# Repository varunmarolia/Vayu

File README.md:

# Vayu
Vayu is a smart ventilation system with heat recovery

# Problem
During winter time when the temperature is in single digit or below, the windows are kept shut and sealed so that radiators can work their magic.
The quality of indoor air gets very bad as the day goes by. The current ventilation system is basically a hole (ranging rom 100mm to 150mm in diameter) in the wall with some filter and vent with open/close mechanism.
This system does not provide enough air flow inside room specifically when the room is sealed. In order to make the indoor quality better the air needs to be forced/pumped inside the room.
Since the outside temperature is very low it needs to be heated and filtered before it can be pulled inside the room. 

# Focus of the project
- The aim of the project is to provide a ventilation system that can provide fresh room temperature air. We do this by recovering the heat from the air in the room itself.
- The system must be smart enough such that the "Heat recovery" should be performed automatically. i.e. if the outside temperature air is cold, turn on the heat recovery, if not just do normal ventilation.
- The design must be a quiet one, so we can sleep peacefully.
- Proper condensation management and defrosting functions.
- The system should have wireless capabilities in order to be an IoT device in the future.

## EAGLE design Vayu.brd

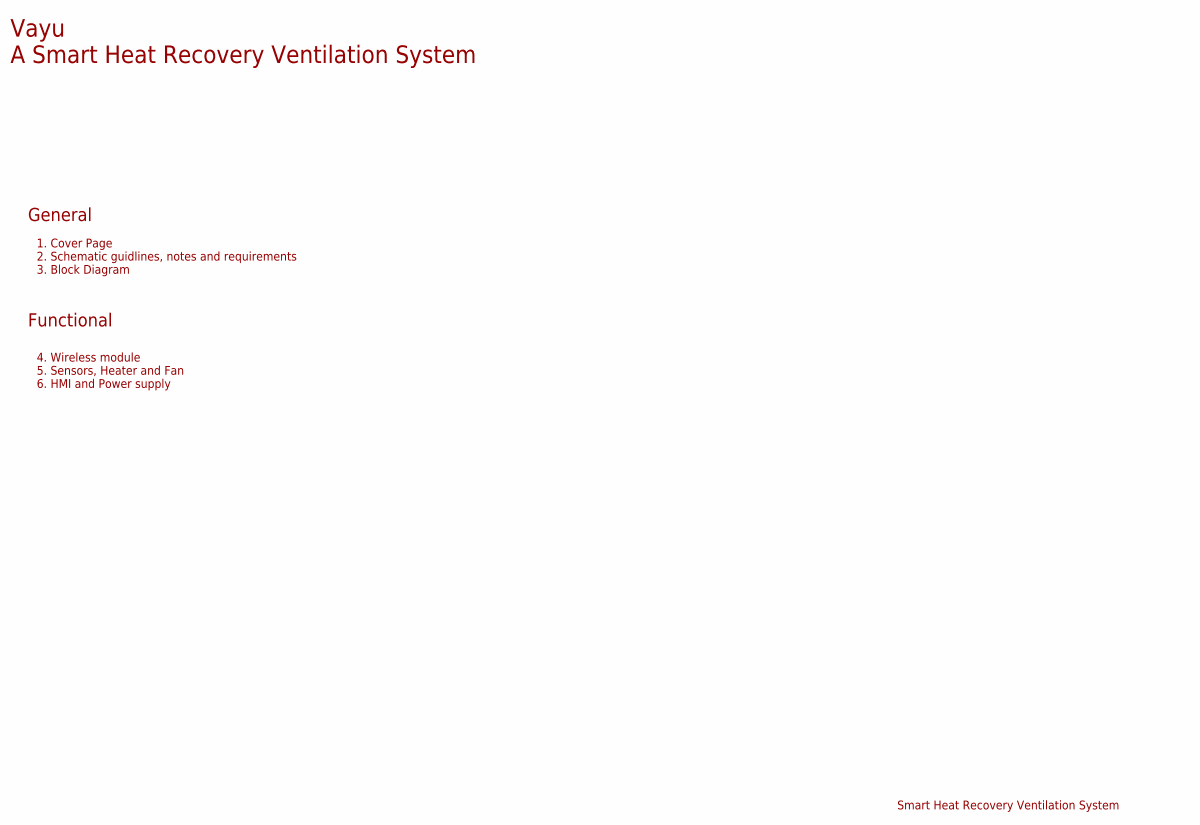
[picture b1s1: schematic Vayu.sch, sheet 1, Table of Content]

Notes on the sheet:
Smart Heat Recovery Ventilation System
General
1. Cover Page 2. Schematic guidlines, notes and requirements 3. Block Diagram
Functional
4. Wireless module 5. Sensors, Heater and Fan 6. HMI and Power supply
Vayu A Smart Heat Recovery Ventilation System

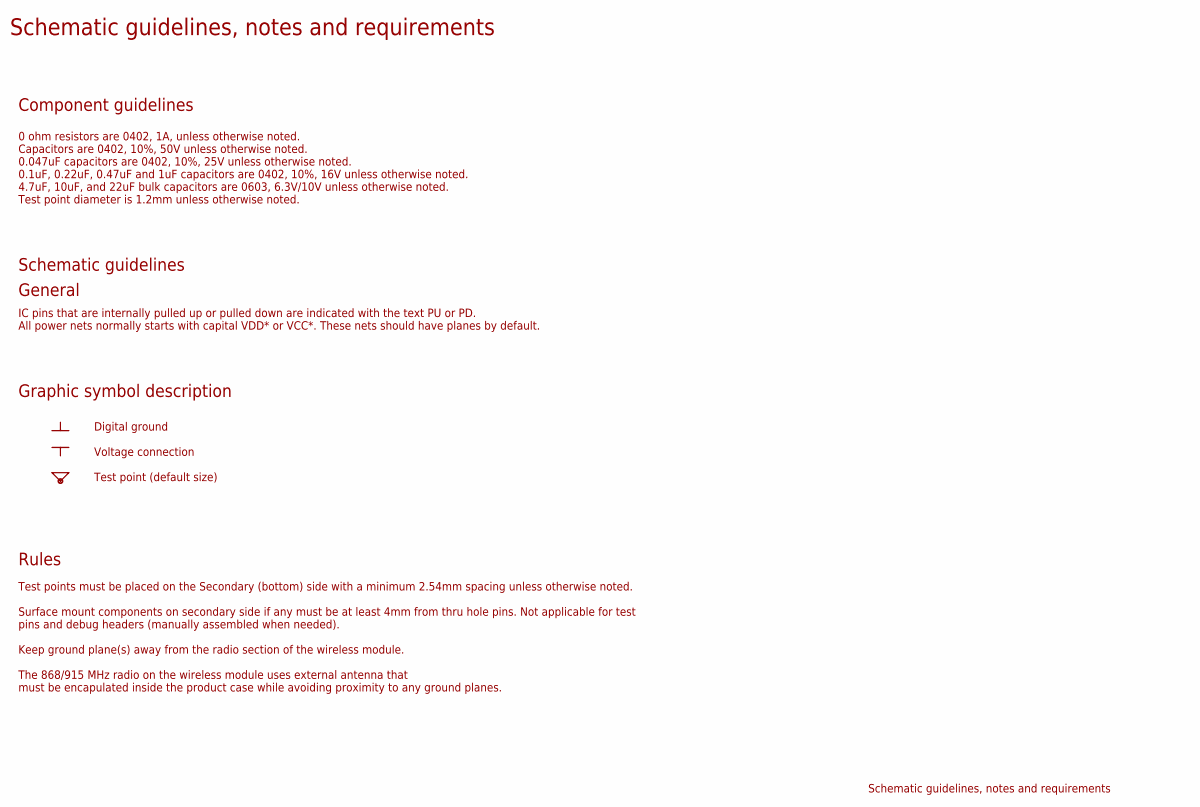
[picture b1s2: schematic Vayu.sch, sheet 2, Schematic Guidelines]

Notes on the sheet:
Schematic guidelines, notes and requirements
Component guidelines
0 ohm resistors are 0402, 1A, unless otherwise noted. Capacitors are 0402, 10%, 50V unless otherwise noted. 0.047uF capacitors are 0402, 10%, 25V unless otherwise noted. 0.1uF, 0.22uF, 0.47uF and 1uF capacitors are 0402, 10%, 16V unless otherwise noted. 4.7uF, 10uF, and 22uF bulk capacitors are 060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
Schematic guidelines
General
IC pins that are internally pulled up or pulled down are indicated with the text PU or PD. All power nets normally starts with capital VDD* or VCC*. These nets should have planes by default.
Graphic symbol description
Digital ground Voltage connection Test point (default size)
Rules
Test points must be placed on the Secondary (bottom) side with a minimum 2.54mm spacing unless otherwise noted. Surface mount components on secondary side if any must be at least 4mm from thru hole pins. Not applicable for test pins and debug headers (manually assembled when needed). Keep ground pl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

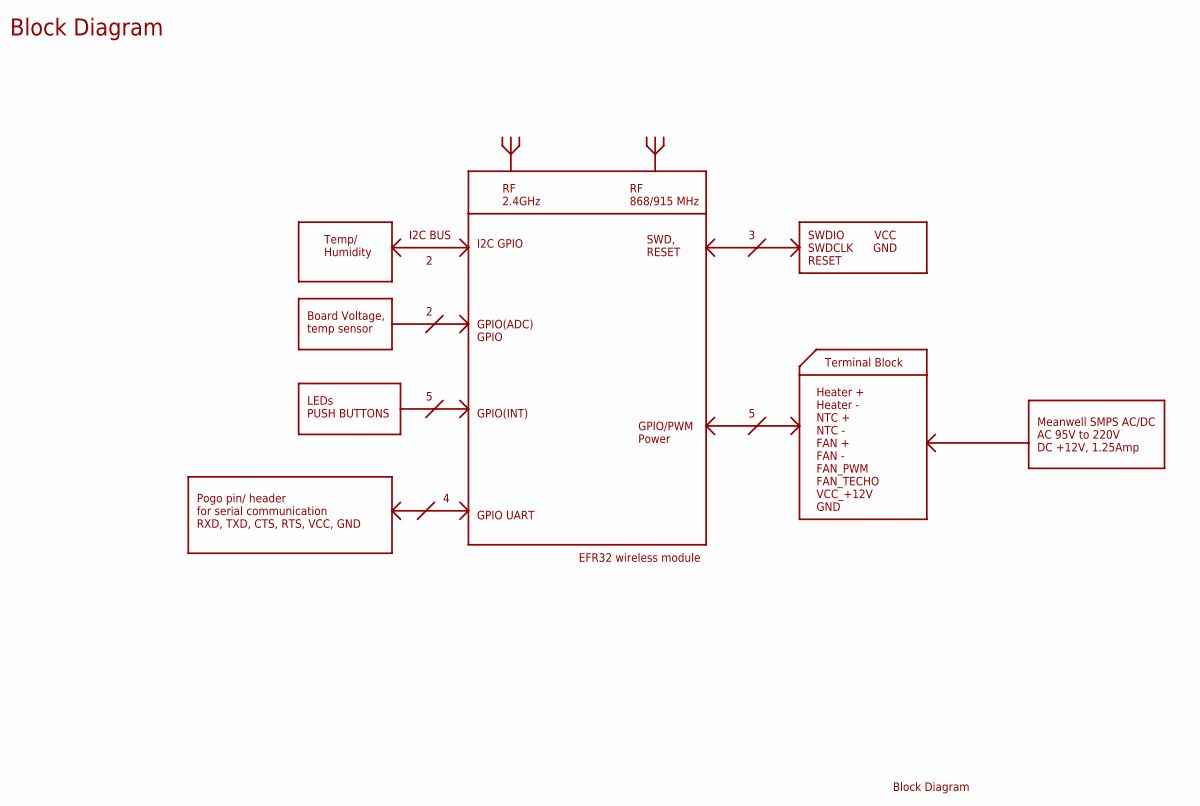
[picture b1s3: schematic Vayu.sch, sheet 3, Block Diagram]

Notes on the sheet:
Block Diagram
RF 2.4GHz
RF 868/915 MHz
SWD, RESET
SWDIO VCC SWDCLK GND RESET
Terminal Block
Heater + Heater - NTC + NTC - FAN + FAN - FAN_PWM FAN_TECHO VCC_+12V GND
Meanwell SMPS AC/DC AC 95V to 220V DC +12V, 1.25Amp
GPIO/PWM Power
GPIO UART
Pogo pin/ header for serial communication RXD, TXD, CTS, RTS, VCC, GND
I2C BUS
Temp/ Humidity
Board Voltage, temp sensor
LEDs PUSH BUTTONS
I2C GPIO
GPIO(ADC) GPIO
GPIO(INT)
EFR32 wireless module

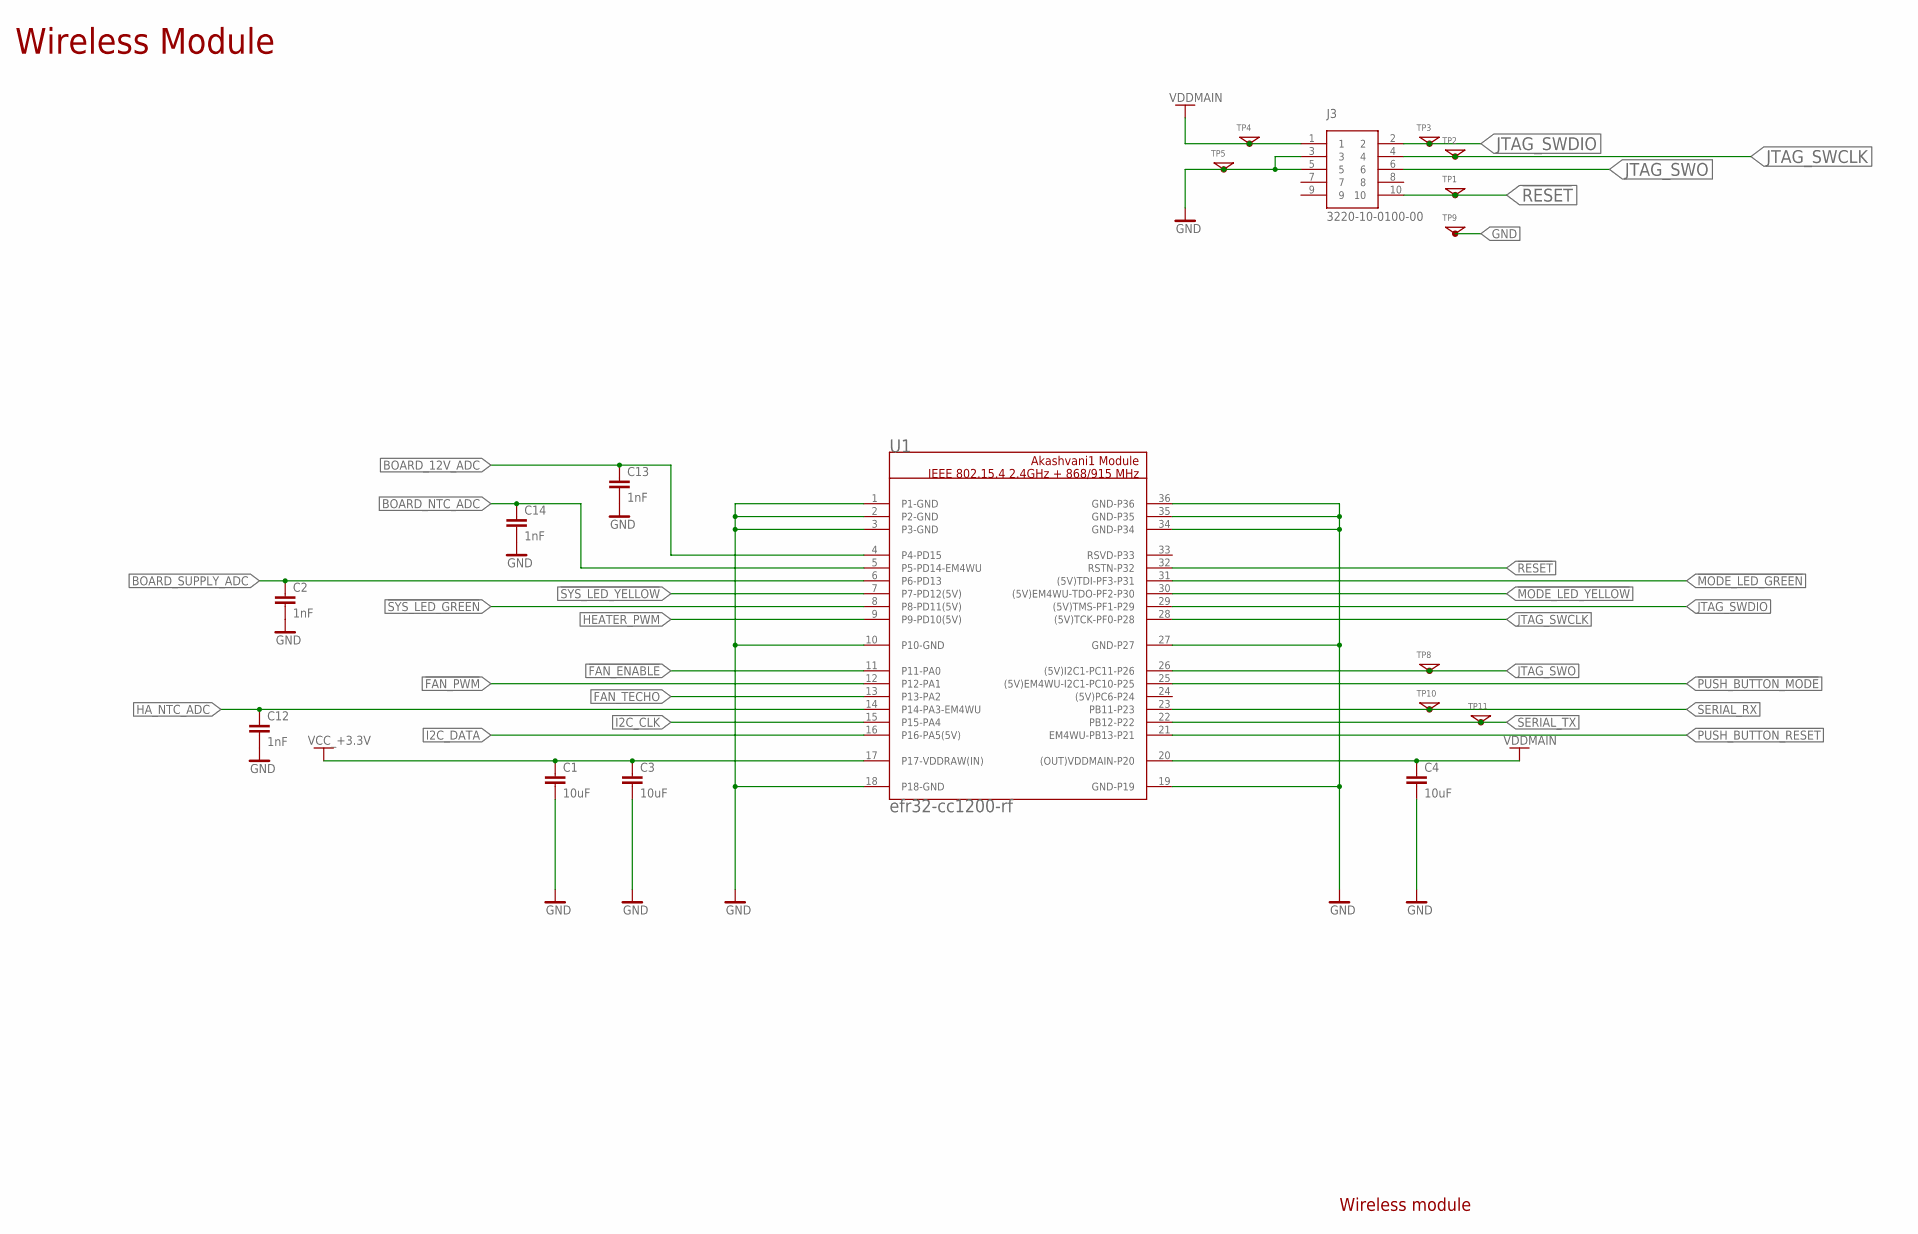
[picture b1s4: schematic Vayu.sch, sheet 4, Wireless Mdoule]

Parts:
C1, C3, C4: 10uF; C0603
C2, C12, C13, C14: 1nF; CAPC1005X55N
J3: 3220-10-0100-00; PIN2X5_1.27MM
TP1, TP2, TP3, TP4, TP5, TP8, TP9, TP10, TP11: TP_1.2
U1: efr32-cc1200-rf; AKASHVANI1

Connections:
!FAN_ENABLE: U1.11 (P11-PA0); also elsewhere on the board
!FAN_PWM: U1.12 (P12-PA1); also elsewhere on the board
!MODE_LED_GREEN: U1.31 ((5V)TDI-PF3-P31); also elsewhere on the board
!MODE_LED_YELLOW: U1.30 ((5V)EM4WU-TDO-PF2-P30); also elsewhere on the board
!PUSH_BUTTON_MODE: U1.25 ((5V)EM4WU-I2C1-PC10-P25); also elsewhere on the board
!PUSH_BUTTON_RESET: U1.21 (EM4WU-PB13-P21); also elsewhere on the board
!RESET: J3.10, TP1.1, U1.32 (RSTN-P32)
!SYS_LED_GREEN: U1.8 (P8-PD11(5V)); also elsewhere on the board
!SYS_LED_YELLOW: U1.7 (P7-PD12(5V)); also elsewhere on the board
BOARD_12V_ADC: C13.1, U1.4 (P4-PD15); also elsewhere on the board
BOARD_NTC_ADC: C14.1, U1.5 (P5-PD14-EM4WU); also elsewhere on the board
BOARD_SUPPLY_ADC: C2.1, U1.6 (P6-PD13); also elsewhere on the board
FAN_TECHO: U1.13 (P13-PA2); also elsewhere on the board
GND: C1.2, C2.2, C3.2, C4.2, C12.2, C13.2, C14.2, J3.3, J3.5, TP5.1, TP9.1, U1.1 (P1-GND), U1.2 (P2-GND), U1.3 (P3-GND), U1.10 (P10-GND), U1.18 (P18-GND), U1.19 (GND-P19), U1.27 (GND-P27), U1.34 (GND-P34), U1.35 (GND-P35), U1.36 (GND-P36); also elsewhere on the board
HA_NTC_ADC: C12.1, U1.14 (P14-PA3-EM4WU); also elsewhere on the board
HEATER_PWM: U1.9 (P9-PD10(5V)); also elsewhere on the board
I2C_CLK: U1.15 (P15-PA4); also elsewhere on the board
I2C_DATA: U1.16 (P16-PA5(5V)); also elsewhere on the board
JTAG_SWCLK: J3.4, TP2.1, U1.28 ((5V)TCK-PF0-P28)
JTAG_SWDIO: J3.2, TP3.1, U1.29 ((5V)TMS-PF1-P29)
JTAG_SWO: J3.6, TP8.1, U1.26 ((5V)I2C1-PC11-P26)
SERIAL_RX: TP10.1, U1.23 (PB11-P23)
SERIAL_TX: TP11.1, U1.22 (PB12-P22)
VCC_+3.3V: C1.1, C3.1, U1.17 (P17-VDDRAW(IN)); also elsewhere on the board
VDDMAIN: C4.1, J3.1, TP4.1, U1.20 ((OUT)VDDMAIN-P20); also elsewhere on the board

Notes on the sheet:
Wireless module
Wireless Module

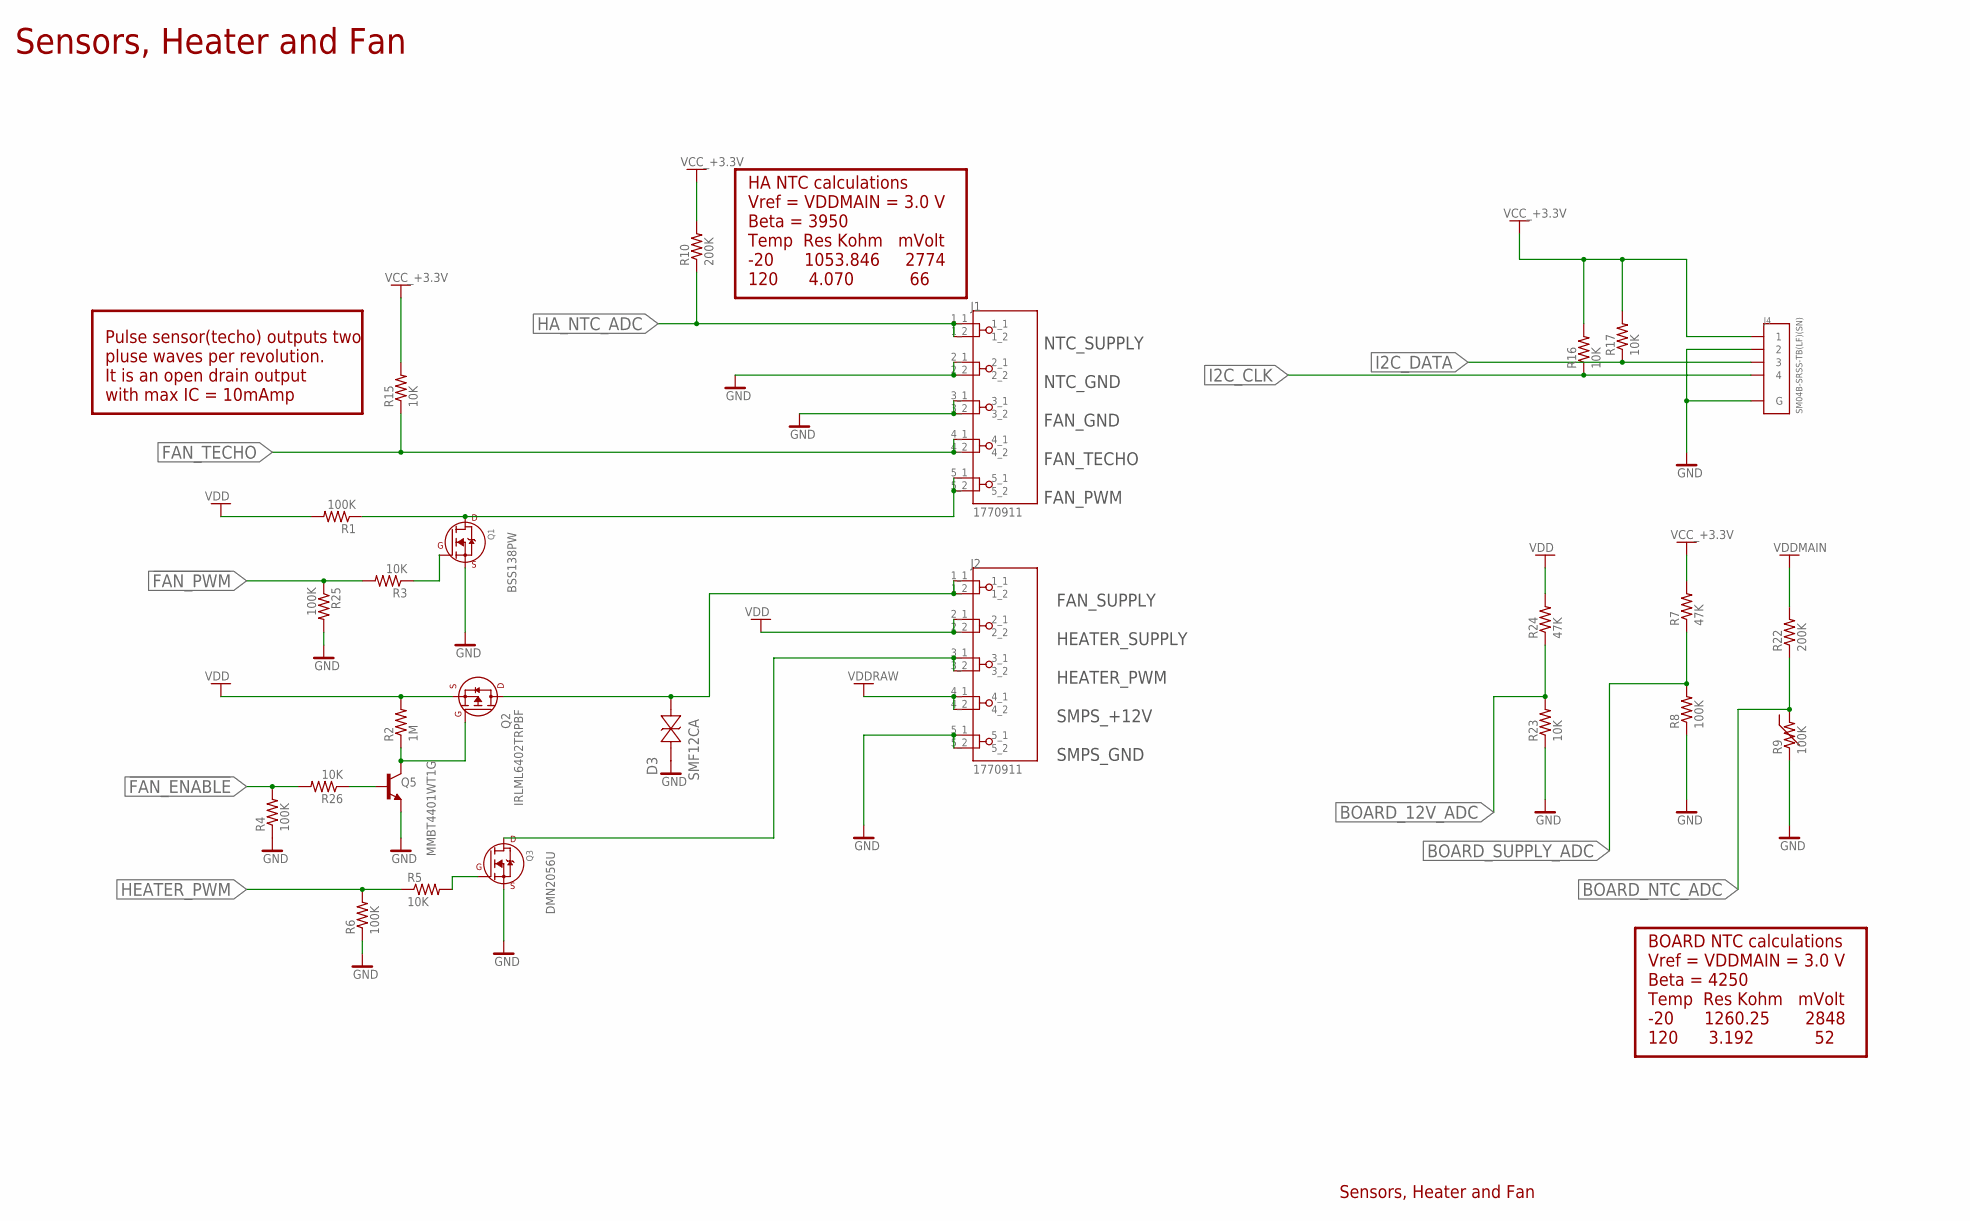
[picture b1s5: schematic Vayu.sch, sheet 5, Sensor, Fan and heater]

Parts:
D3: SMF12CA; SOD-123F-BI
J1, J2: 1770911; PHOENIX_1770911
J4: SM04B-SRSS-TB(LF)(SN); JST_SM04B-SRSS-TB(LF)(SN)
Q1: BSS138PW; SC-70_SOT323
Q2: IRLML6402TRPBF; SOT23-3
Q3: DMN2056U; SOT23-3
Q5: MMBT4401WT1G; SOT323-BEC
R1, R4, R6, R8, R9, R25: 100K; R0402
R2: 1M; R0402
R3, R5, R15, R16, R17, R23, R26: 10K; R0402
R7, R24: 47K; R0402
R10, R22: 200K; R0402

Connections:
!FAN_ENABLE: R4.2, R26.2; also elsewhere on the board
!FAN_PWM: R3.2, R25.1; also elsewhere on the board
BOARD_12V_ADC: R23.2, R24.1; also elsewhere on the board
BOARD_NTC_ADC: R9.2, R22.1; also elsewhere on the board
BOARD_SUPPLY_ADC: R7.1, R8.2; also elsewhere on the board
FAN_SPEED: J1.5_1, J1.5_2, Q1.3 (D), R1.1
FAN_SUPPLY: D3.1 (11), J2.1_1, J2.1_2, Q2.D
FAN_TECHO: J1.4_1, J1.4_2, R15.1; also elsewhere on the board
GND: D3.2 (12), J1.2_1, J1.2_2, J1.3_1, J1.3_2, J2.5_1, J2.5_2, J4.2, J4.S1 (G), J4.S2 (G), Q1.2 (S), Q3.S, Q5.E, R4.1, R6.1, R8.1, R9.1, R23.1, R25.2; also elsewhere on the board
HA_NTC_ADC: J1.1_1, J1.1_2, R10.1; also elsewhere on the board
HEATER: J2.3_1, J2.3_2, Q3.D
HEATER_PWM: R5.1, R6.2; also elsewhere on the board
I2C_CLK: J4.4, R16.1; also elsewhere on the board
I2C_DATA: J4.3, R17.1; also elsewhere on the board
unnamed: Q1.1 (G), R3.1
unnamed: Q3.G, R5.2
unnamed: Q5.B, R26.1
PMOSFET_EN: Q2.G, Q5.C, R2.1
VCC_+3.3V: J4.1, R7.2, R10.2, R15.2, R16.2, R17.2; also elsewhere on the board
VDD: J2.2_1, J2.2_2, Q2.S, R1.2, R2.2, R24.2; also elsewhere on the board
VDDMAIN: R22.2; also elsewhere on the board
VDDRAW: J2.4_1, J2.4_2; also elsewhere on the board

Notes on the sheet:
Sensors, Heater and Fan
Pulse sensor(techo) outputs two pluse waves per revolution. It is an open drain output with max IC = 10mAmp
NTC_SUPPLY NTC_GND FAN_GND FAN_TECHO FAN_PWM
FAN_SUPPLY HEATER_SUPPLY HEATER_PWM SMPS_+12V SMPS_GND
HA NTC calculations Vref = VDDMAIN = 3.0 V Beta = 3950 Temp Res Kohm mVolt -20 1053.846 2774 120 4.070 66
BOARD NTC calculations Vref = VDDMAIN = 3.0 V Beta = 4250 Temp Res Kohm mVolt -20 1260.25 2848 120 3.192 52

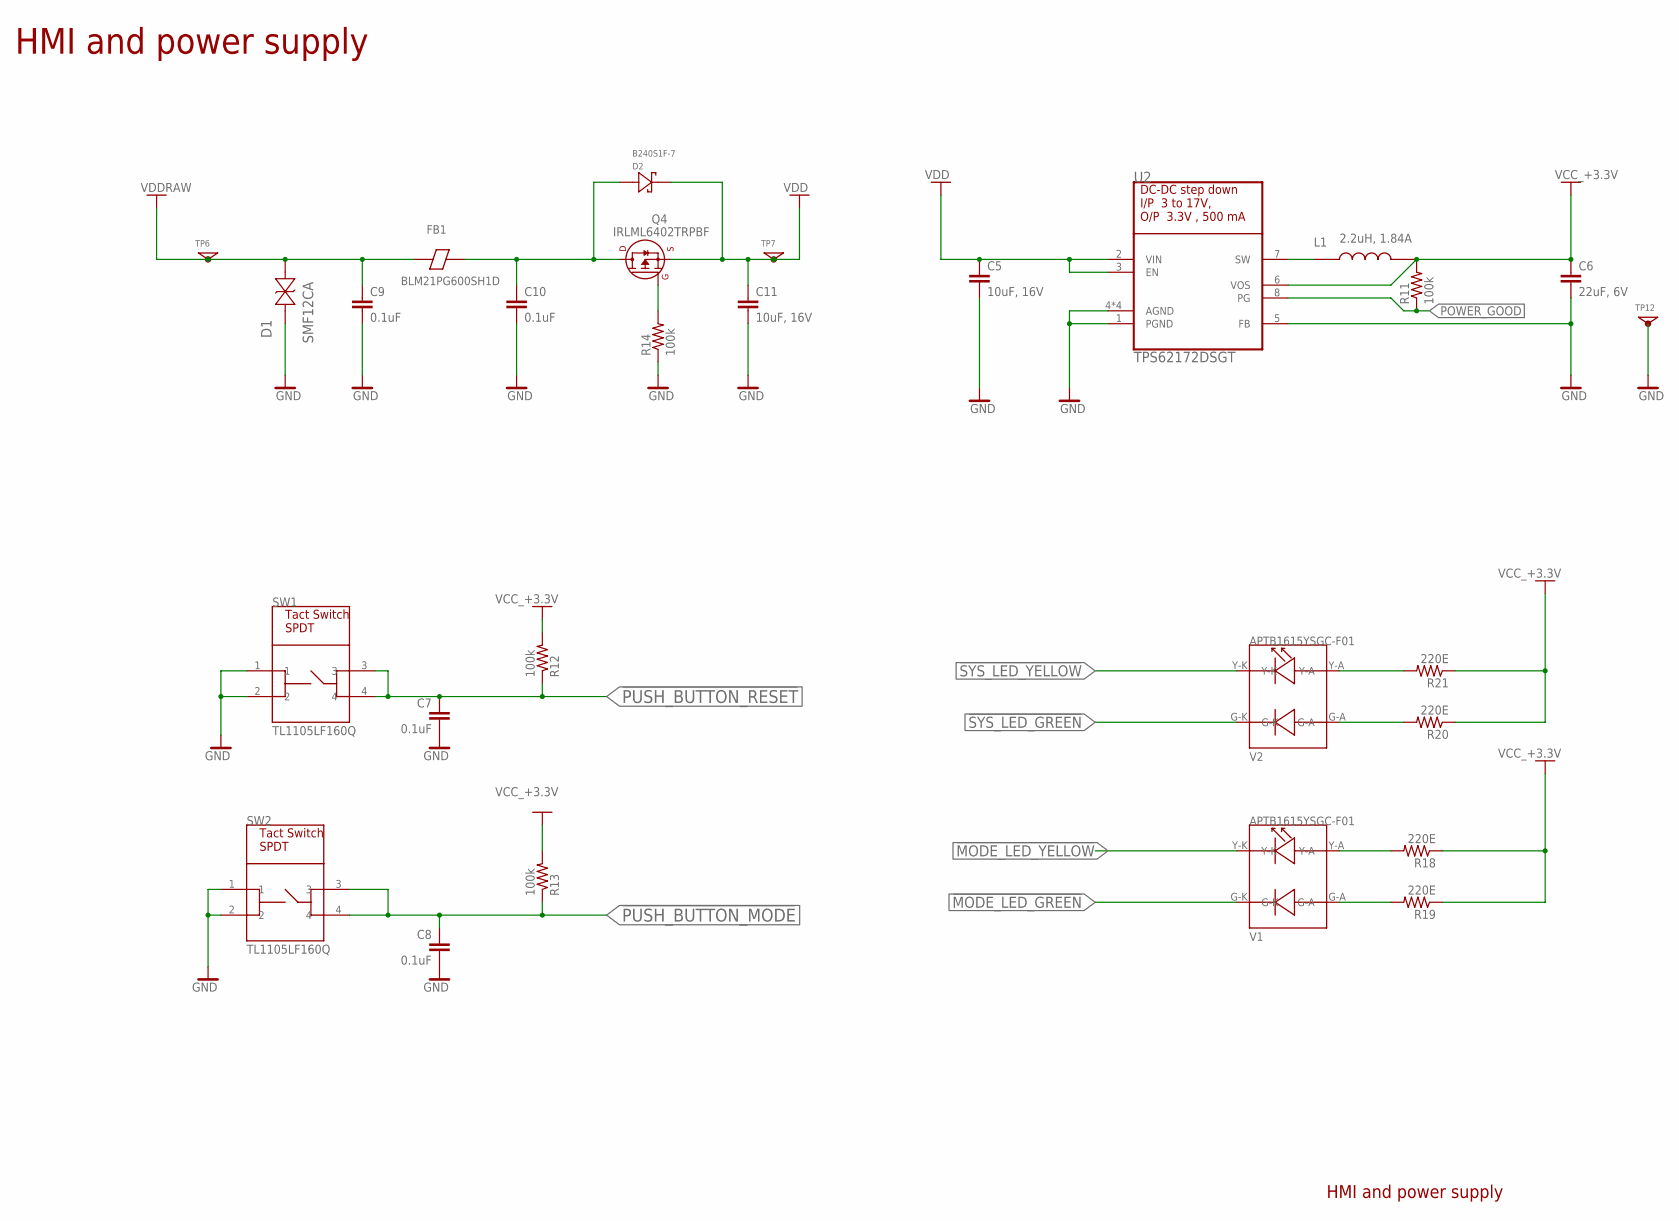
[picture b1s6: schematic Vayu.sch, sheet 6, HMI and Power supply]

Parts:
C5, C11: 10uF, 16V; C0805
C6: 22uF, 6V; C0603
C7, C8, C9, C10: 0.1uF; CAPC1005X55N
D1: SMF12CA; SOD-123F-BI
D2: B240S1F-7; SOD-123F
FB1: BLM21PG600SH1D; BEADC2012X105N
L1: 2.2uH, 1.84A; IND_VLS201612HBX-2R2M-1
Q4: IRLML6402TRPBF; SOT23-3
R11, R12, R13, R14: 100k; R0402
R18, R19, R20, R21: 220E; R0402
SW1, SW2: TL1105LF160Q; TACT_TH_6X6X17MM
TP6, TP7, TP12: TP_1.2
U2: TPS62172DSGT; SON50P200X200X80-9N
V1, V2: APTB1615YSGC-F01; LED-0606

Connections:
!MODE_LED_GREEN: V1.G-K; also elsewhere on the board
!MODE_LED_YELLOW: V1.Y-K; also elsewhere on the board
!PUSH_BUTTON_MODE: C8.1, R13.1, SW2.3, SW2.4; also elsewhere on the board
!PUSH_BUTTON_RESET: C7.1, R12.1, SW1.3, SW1.4; also elsewhere on the board
!SYS_LED_GREEN: V2.G-K; also elsewhere on the board
!SYS_LED_YELLOW: V2.Y-K; also elsewhere on the board
GND: C5.2, C6.2, C7.2, C8.2, C9.2, C10.2, C11.2, D1.2 (12), R14.1, SW1.1, SW1.2, SW2.1, SW2.2, TP12.1, U2.1 (PGND), U2.4 (AGND), U2.5 (FB), U2.9 (AGND), U2.9_1 (AGND), U2.9_2 (AGND); also elsewhere on the board
unnamed: L1.1, U2.7 (SW)
unnamed: C10.1, D2.A, FB1.2, Q4.D
unnamed: Q4.G, R14.2
unnamed: R21.2, V2.Y-A
unnamed: R20.2, V2.G-A
unnamed: R18.2, V1.Y-A
unnamed: R19.2, V1.G-A
POWER_GOOD: R11.1, U2.8 (PG)
VCC_+3.3V: C6.1, L1.2, R11.2, R12.2, R13.2, R18.1, R19.1, R20.1, R21.1, U2.6 (VOS); also elsewhere on the board
VDD: C5.1, C11.1, D2.K, Q4.S, TP7.1, U2.2 (VIN), U2.3 (EN); also elsewhere on the board
VDDRAW: C9.1, D1.1 (11), FB1.1, TP6.1; also elsewhere on the board

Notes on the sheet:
HMI and power supply

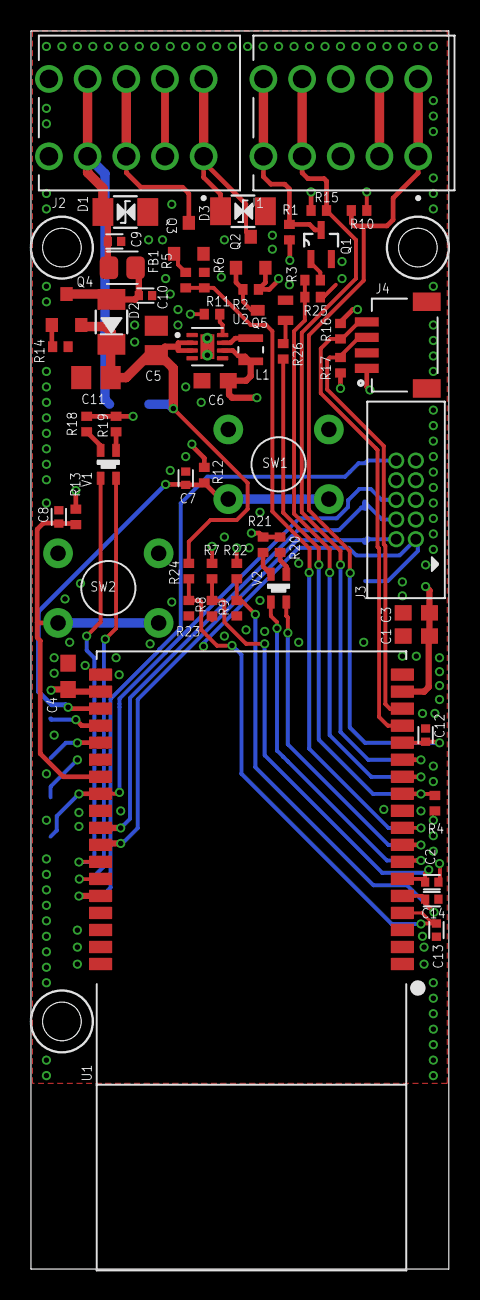
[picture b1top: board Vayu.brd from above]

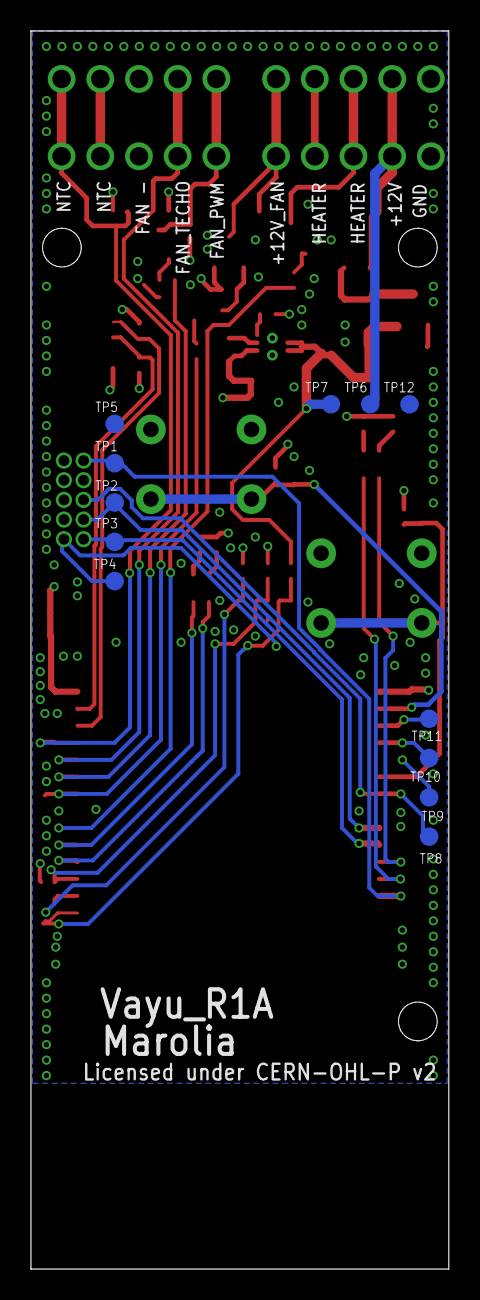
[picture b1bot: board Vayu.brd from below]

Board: 4 copper layers, 27.0 x 80.0 mm, 72 parts (12 on the bottom side), 42 nets.

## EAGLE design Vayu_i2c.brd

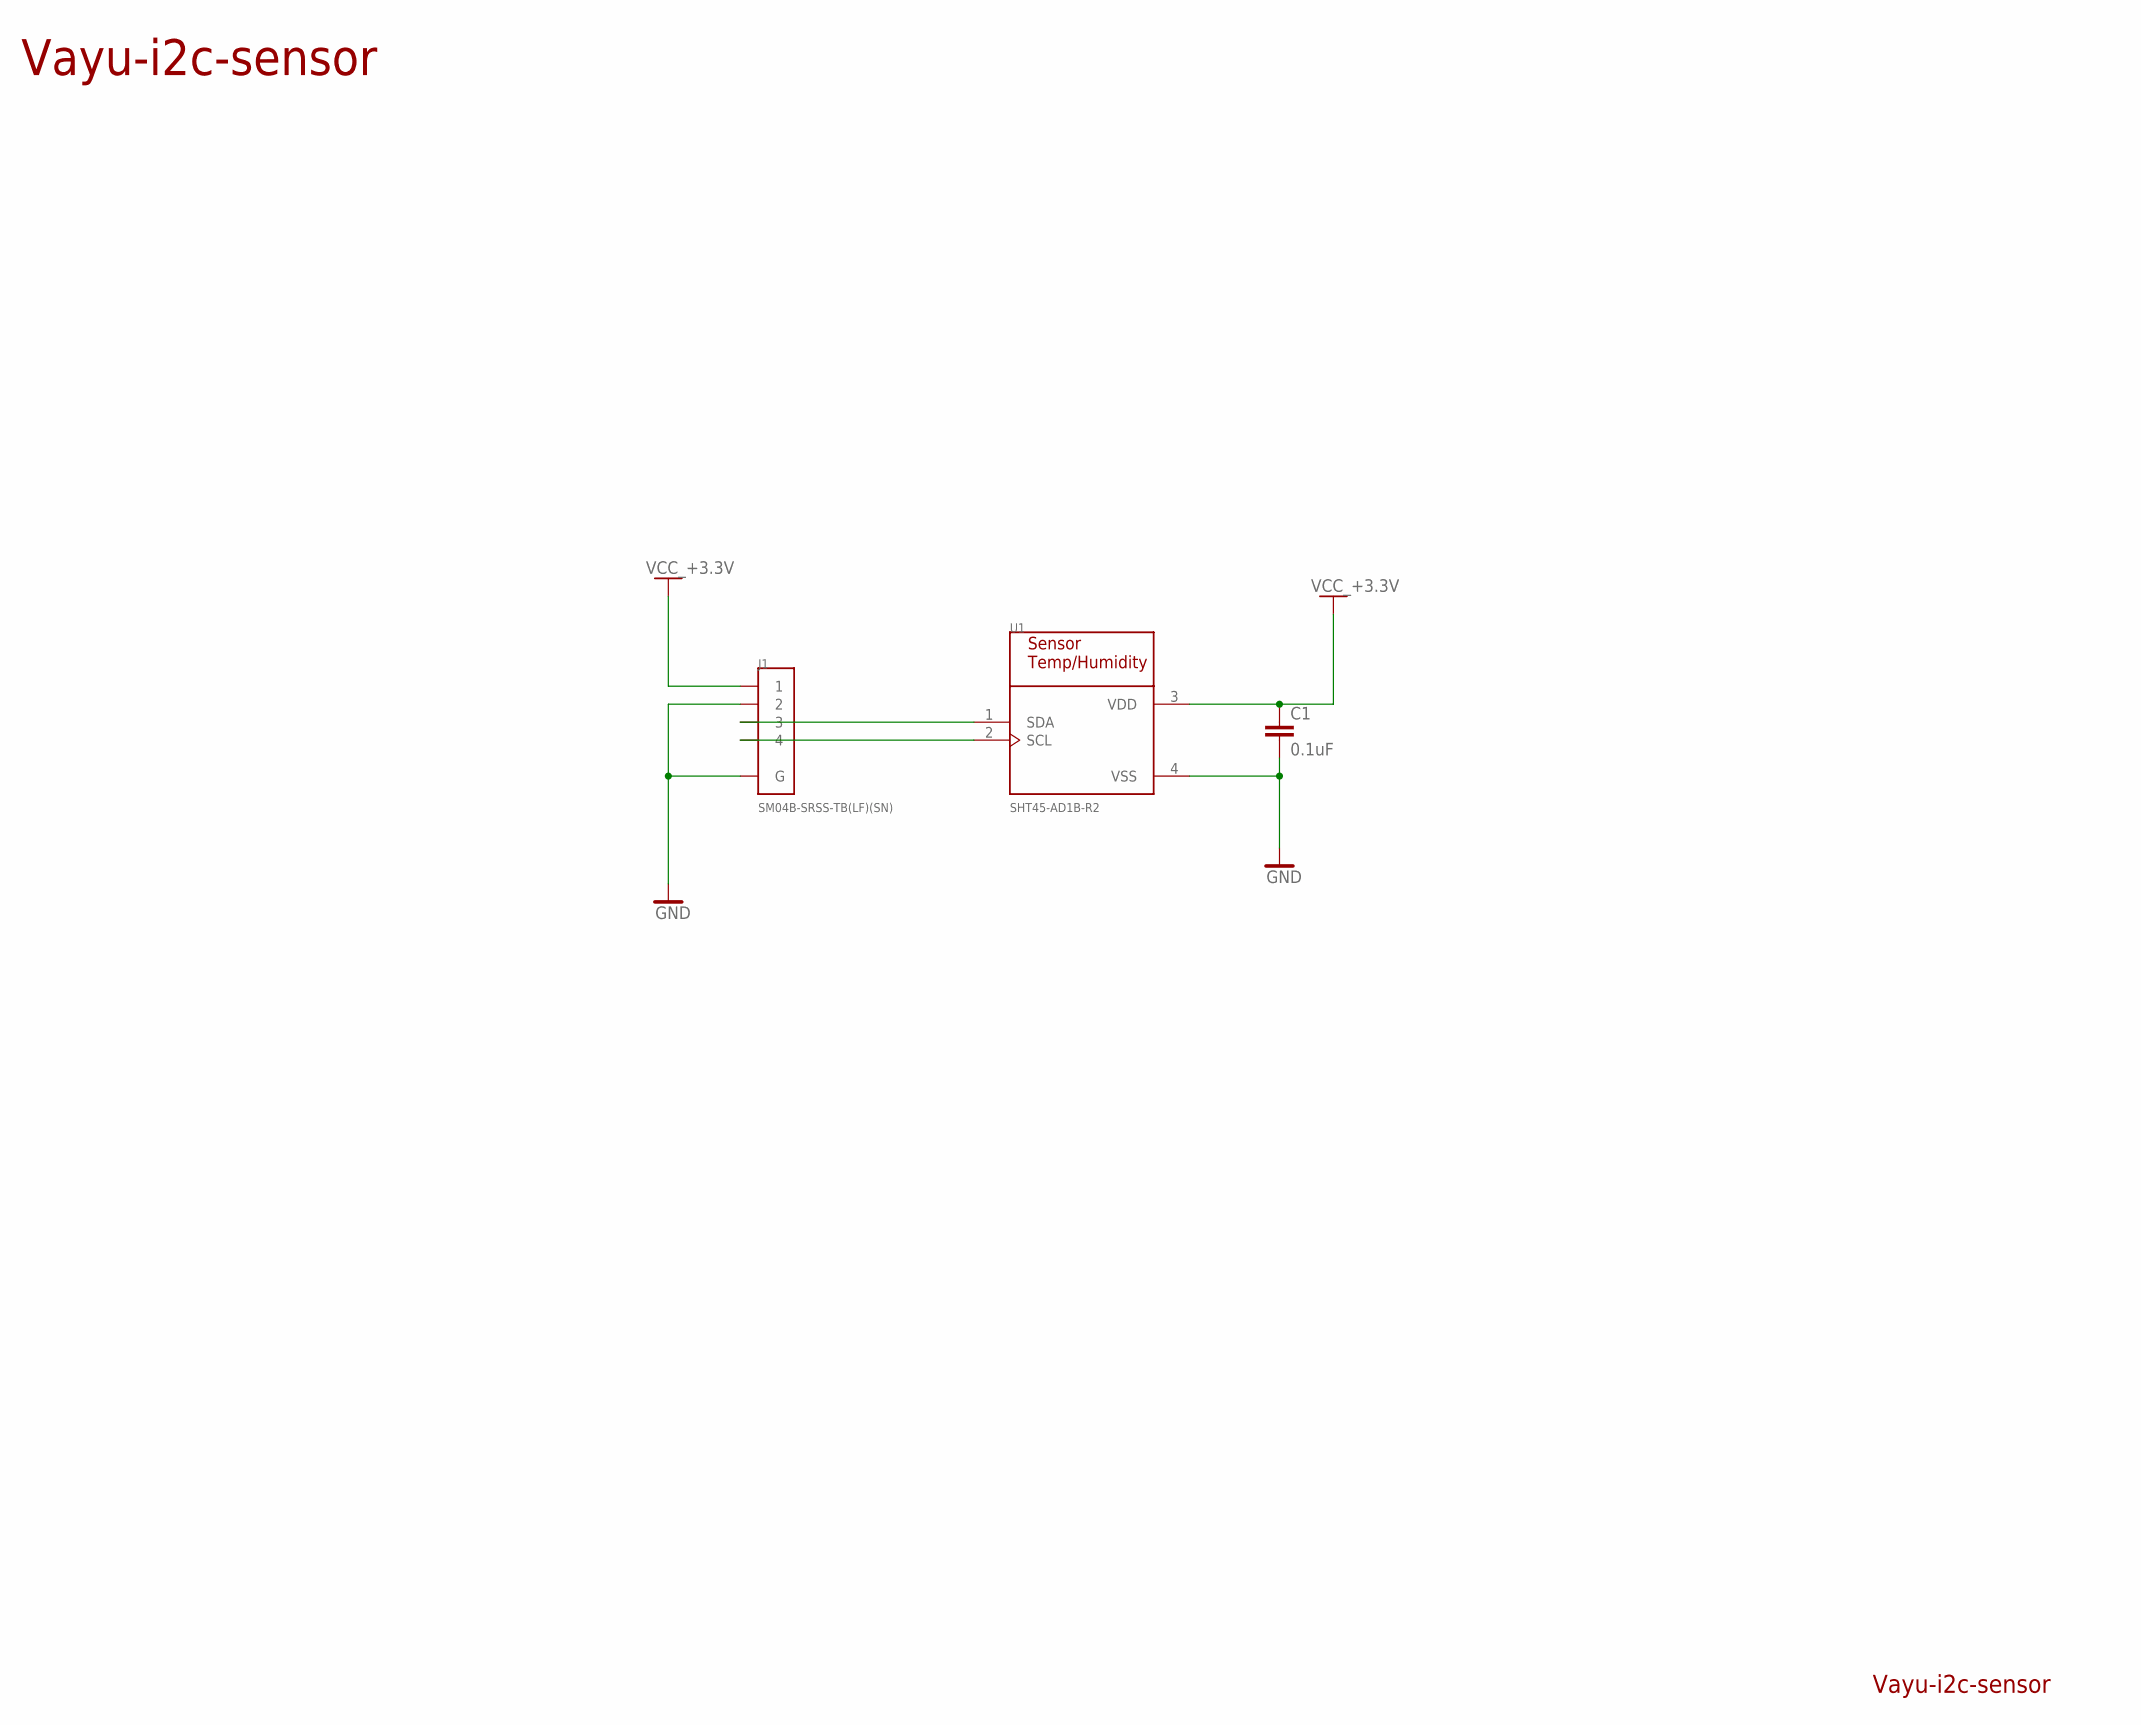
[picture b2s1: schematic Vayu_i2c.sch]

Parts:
C1: 0.1uF; C0402
J1: SM04B-SRSS-TB(LF)(SN); JST_SM04B-SRSS-TB(LF)(SN)
U1: SHT45-AD1B-R2; XDCR_SHT45-AD1B-R2

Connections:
GND: C1.2, J1.2, J1.S1 (G), J1.S2 (G), U1.4 (VSS)
unnamed: J1.3, U1.1 (SDA)
unnamed: J1.4, U1.2 (SCL)
VCC_+3.3V: C1.1, J1.1, U1.3 (VDD)

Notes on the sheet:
Vayu-i2c-sensor

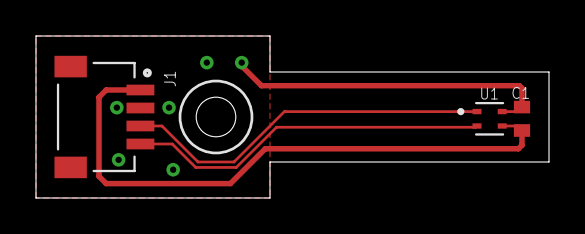
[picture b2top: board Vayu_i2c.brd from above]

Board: 2 copper layers, 28.5 x 9.0 mm, 3 parts (0 on the bottom side), 4 nets.

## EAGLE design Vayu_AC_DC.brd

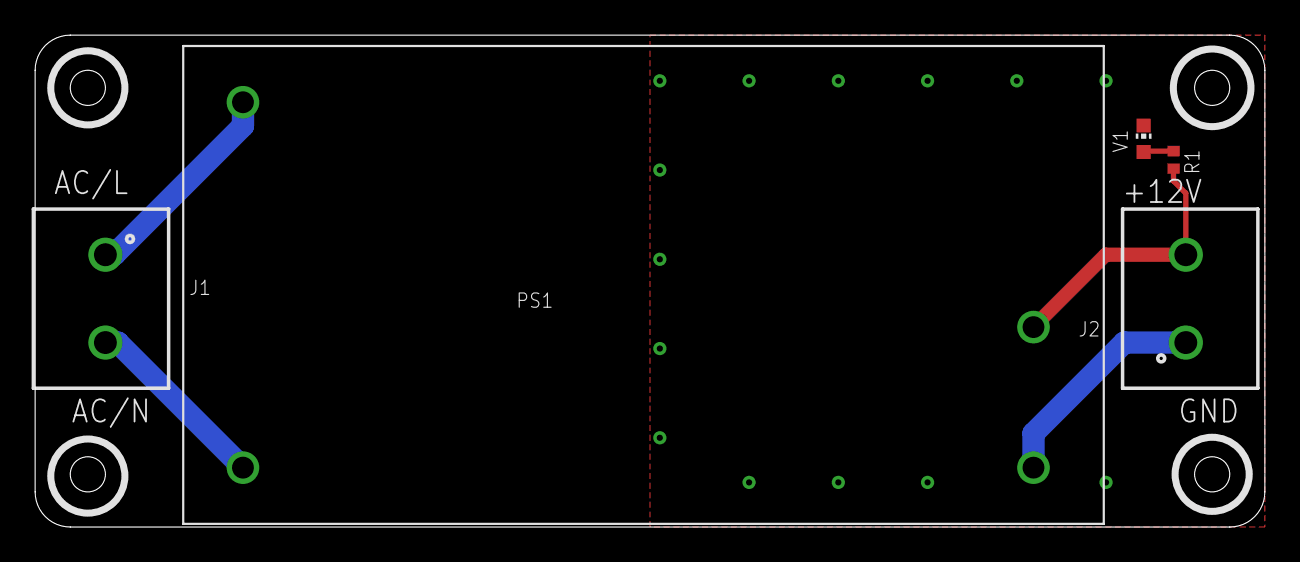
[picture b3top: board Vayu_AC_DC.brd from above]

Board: 2 copper layers, 70.0 x 28.0 mm, 5 parts (0 on the bottom side), 5 nets.

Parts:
J1, J2: 691137710002
PS1: IRM-15-12; CONV_IRM-15-12
R1: 680R; R0402
V1: RED; CHIP-LED0603

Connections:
AC/L: J1.1, PS1.AC/L
AC/N: J1.2, PS1.AC/N
GND: J2.1, PS1.-V, V1.C
unnamed: R1.1, V1.A
VDD: J2.2, PS1.+V, R1.2

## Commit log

2025-01-14 Last 3 months work !
2025-01-15 Added ignore and new raw files after complete data loss!
2025-01-15 Added gerber files updated schematic files
2025-01-15 updated read me files
2025-01-15 Added dru, updated board thermal mask, added Vayu bom file
2025-01-16 Added BOM files for sensor, AC-DC and top level
2025-01-16 Added magnet
2025-01-17 Added heater,tape and NTC
2025-03-12 removed sch bugs and WIP in brd
2025-03-14 bug fix, updated MOSFET driver and other MOSFETS, added SWO support

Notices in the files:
Vayu.brd:
Licensed under CERN-OHL-P v2
parts and their libraries:
frames: Copyright CERN 2020.
This source describes Open Hardware and is licensed under the CERN-OHL-P v2
using it under the terms of the CERN-OHL-P v2 (https:/cern.ch/cern-ohl).
frames: A3 size Tabel of Content for Open source hardware project Licensed under CERN open hardware permisive V2 license
